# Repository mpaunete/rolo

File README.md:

# ROLO

A two-wheeled self-balancing robot built around an ESP32, with stepper motors, a servo arm,
a Bluetooth gamepad, live telemetry over WiFi, and the ability to stand itself up after a fall.

> **Early version, work in progress.** The electronics mostly work: you can pair a gamepad
> and drive ROLO around, and it balances and stands itself up. But this is a first version,
> some improvements are already needed, and much is still being built, tuned and redesigned.
> Expect things to change, and some parts of this repository to be incomplete.
> See [Current status](#current-status).

## Inspiration and goals

ROLO started from the [JJRobots B-Robot EVO 2](https://www.jjrobots.com/b-robot-evo-2-much-more-than-a-self-balancing-robot/)
and the [Kidbuild balance robot kit](https://www.kidbuild.de/balance-robot-kit/). I decided to
rebuild them and improve the electronics, with these goals:

- **Quieter motors:** TMC2209 stepper drivers.
- **Maximum customisation:** most of the parts redesigned in FreeCAD.
- **More sensors and accessories** than the original designs allow.
- **AI experimentation:** a face, voice, vision and a personality, in the spirit of Anki Vector.
- **A 3S battery,** and better battery management later (for example, charging without
  unplugging it).
- **Learning:** about balancing control and about AI on small robots.
- **A robotics platform for kids:** children can program ROLO themselves with
  [UIFlow](https://uiflow2.m5stack.com/) (M5Stack's block editor and MicroPython) on the
  M5Stack head, driving the robot through the same commands as the gamepad and the web pages.

## Videos

The full clip, from the stand-up to driving around:
[rolo-driving.mp4](docs/images/rolo-driving.mp4) (22 s, no sound).

## Current status

| area | status |
|---|---|
| balancing | working, tuned from recorded data |
| driving (gamepad and web joystick) | working; faster driving and steering feel still being tuned |
| standing up from lying face-down | working (arm push + wheel kick), still being refined |
| telemetry, recorder and analysis tools | working |
| web pages (drive, calibration with terminal, gamepad) | working |
| battery warnings | working |
| controller PCB (KiCad) | first version: mostly works, improvements needed (see below); files in `electronics/` |
| mechanical parts (FreeCAD) | designed, not yet published here |
| head: face, camera, microphones (M5Stack CoreS3) | hardware chosen, firmware not started |
| voice, vision, AI | planned |
| second robot and games | planned |
| battery management (charging in place) | planned |
| kids' programming (UIFlow on the M5Stack head) | planned |

### Known issues in the first electronics version

- The servo shares the 5 V supply with the logic. When it pulls hard, the supply dips enough
  to disturb WiFi and the IMU. A capacitor at the servo, or a separate supply for it, is needed.
- Few spare GPIOs are left on the controller for new sensors and accessories.
- No charging in place yet: the battery has to be unplugged to charge.

The planned fixes for the electronics and the mechanical parts are listed in
[docs/next-revision.md](docs/next-revision.md).

## Features

- **Balancing** with a cascaded controller: an angle loop (PD on a filtered gyro) inside a
  speed loop, with an acceleration feed-forward so the robot leans into speed changes.
- **Driving** from a gamepad or a web joystick, with a speed ramp shared by acceleration and
  braking.
- **Standing up** from lying face-down: the arm pushes the body up, a wheel kick drives under
  it, and the balance loop takes over mid-way, braking with a deeper lean afterwards.
- **Safety**: tilt cut-off, runaway detection, a command timeout, and battery warnings
  (LEDs and web pages).
- **Web pages** served by the robot: drive (joystick), calibration (live values, parameters,
  a terminal), and a gamepad debug page.
- **200 Hz telemetry stream** with a PC recorder and an analysis script, used to tune
  everything from measured data.
- **One command console** shared by the serial port and the web terminal.

## Repository layout

| folder | contents |
|---|---|
| `firmware/controller/` | the body's firmware: balancing, driving, arm, stand-up, web pages (PlatformIO, C++) |
| `firmware/common/link/` | shared by the body and the heads: the messages on the body–head UART link |
| `firmware/head-c3lcd/` | head: ESP32-C3 SuperMini with a Waveshare 2" LCD (the current head; code to be added) |
| `firmware/head-cores3/` | head: M5Stack CoreS3 (face, camera, microphones, speaker) |
| `firmware/head-seeed/` | head: ESP32-S3 DevKitC with a Seeed Grove Vision AI V2 and a ReSpeaker Lite |
| `firmware/tools/` | `rolo_stream.py` (recorder and test runner), `analyze.py` (report and plots) |
| `electronics/` | KiCad project for the controller board, Gerbers in `Output/` |
| `mechanical/` | mechanical design, FreeCAD (to be added) |
| `docs/` | documentation; [next-revision.md](docs/next-revision.md) lists the planned hardware changes; `images/` has the photos and videos |

## Hardware

| part | notes |
|---|---|
| ESP32 (DevKit V1, classic ESP32) | dual core: control loop on core 1, WiFi/web/LEDs on core 0 |
| 2 × TMC2209 stepper drivers | UART-configured, 1/16 microstepping, 900 mA RMS |
| 2 × NEMA17 steppers (42HD4027-01, 1.5 A) | 93.2 mm wheels |
| MPU6050 IMU | ±1000 °/s gyro, complementary filter |
| hobby servo | the arm (also used to stand up) |
| 3 × WS2812 LEDs | network, robot state, effort / battery warning |
| 3S LiPo | voltage divider (100k/22k) on GPIO 35 |
| Mini560 buck converter | 5 V for the logic and the servo |
| Bluetooth gamepad | a Switch Pro style controller, via Bluepad32 (classic Bluetooth) |

Main pin assignments are in [`firmware/controller/include/config.h`](firmware/controller/include/config.h).

## Building and flashing

Requires [PlatformIO](https://platformio.org/) (the VS Code extension or the CLI).

```bash
cd firmware/controller
pio run -t upload
```

The project uses the Bluepad32 Arduino core (classic Bluetooth gamepad support), which
PlatformIO downloads automatically through `platform_packages` in `platformio.ini`.

## First setup

1. Lay the robot down and power it on. It calibrates the IMU lying still (about 3 s), then
   the status LEDs show the network and robot state.
2. Connect WiFi from the serial console (115200 baud):

   ```
   wifi <ssid> <password>
   net
   ```

   Without a configured network it starts its own access point **`rolo`**
   (password **`rolorolo`**). That password is public, so change it on first use:

   ```
   apname <name>
   appass <password>
   ```

   The password must be at least 8 characters. Both are saved on the robot.
3. Open `http://<robot-ip>/` for the drive page. The calibration page (`/calibration`) has
   the parameters and a terminal; `/gamepad` helps with pairing.
4. Stand the robot up; it starts balancing once it is near upright.

## Console commands

The same commands work on the serial port and in the web terminal (`help` lists them):

| command | what it does |
|---|---|
| `set <name> <value>`, `list`, `save`, `load`, `reset` | tuning parameters (`save` only while lying down) |
| `arm up` / `arm down` | the arm |
| `kick [accel] [speed] [angle]` | stand up from lying face-down |
| `pad pair on\|off`, `pad forget`, `pad rumble` | gamepad pairing |
| `motors`, `motortest <steps/s> [seconds] [accel]` | driver status, spin the wheels with the robot held up |
| `net`, `wifi`, `forget`, `apname`, `appass` | network |
| `mem` | free memory |

## Tools

```bash
cd firmware/tools
python -m venv .venv
.venv/bin/pip install -r requirements.txt

# record 30 s of the 200 Hz stream
.venv/bin/python rolo_stream.py <robot-ip> --seconds 30 --name my-run

# run a repeatable test (still, step, tap, turn, ramp, all) and analyse it
.venv/bin/python rolo_stream.py <robot-ip> --test step --amount 0.5 --name step-1
.venv/bin/python analyze.py step-1
```

Each recording produces `<name>.csv` (samples), `<name>-events.csv` (commands and events) and
`<name>-params.json` (the parameters at the time). `analyze.py` prints a report (timing,
stillness, pushes, drive steps, limits) and saves a plot.

## Roadmap

- **Heads**: interchangeable heads on the same body, linked over UART: a plain ESP32-C3
  with a 2-inch LCD, an M5Stack CoreS3 (face, camera, microphones, speaker) and a Seeed Studio
  vision head. They share one firmware project with a build per head, and each head tells
  the body what it can do. Later: offline voice (wake word and commands), vision, and WiFi
  moved from the body to the head.
- **Optional AI**: a local server for conversation and speech, or an on-robot LLM module.
- **Games**: two robots, a referee page, and living-room battles (knock off the other robot's
  accessories, jousting, IR tag).
- **Kids' programming**: UIFlow on the CoreS3 head, with blocks for driving, the arm, the
  LEDs and the robot's events (fell over, stood up, battery low), so children can write their
  own behaviours and games.

## Licence

[MIT](LICENSE), for now, covering the whole repository. Separate licences for the hardware
files (electronics and mechanical) may follow.

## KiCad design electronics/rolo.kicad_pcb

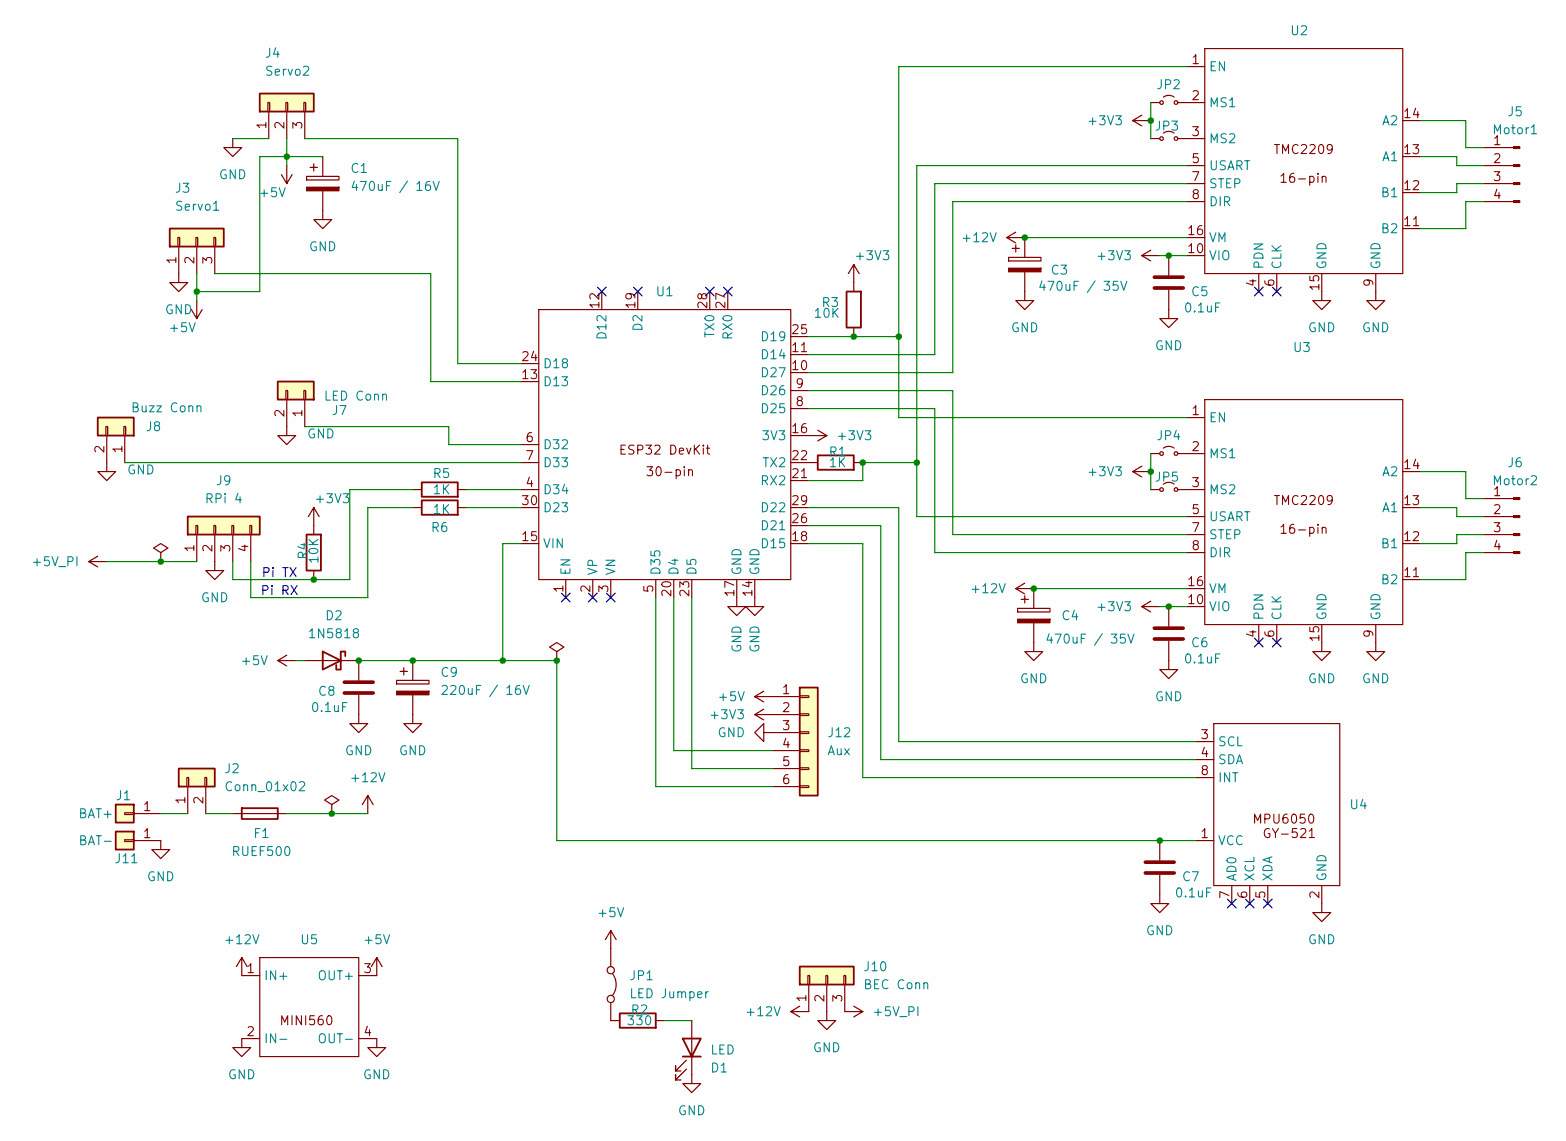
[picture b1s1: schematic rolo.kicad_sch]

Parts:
C1: 470uF / 16V; CP_Radial_D8.0mm_P3.50mm
C3, C4: 470uF / 35V; CP_Radial_D8.0mm_P3.50mm
C5, C6, C7, C8: 0.1uF; C_Disc_D5.0mm_W2.5mm_P5.00mm
C9: 220uF / 16V; CP_Radial_D8.0mm_P3.50mm
D1: LED; LED_D3.0mm
D2: 1N5818; D_DO-41_SOD81_P10.16mm_Horizontal
F1: RUEF500; Fuse_RUEF500
J1: BAT+; MountingHole_2.2mm_M2_Pad
J2: Conn_01x02; AMASS_XT30U-M_1x02_P5.0mm_Vertical
J3: Servo1; PinHeader_1x03_P2.54mm_Vertical
J4: Servo2; PinHeader_1x03_P2.54mm_Vertical
J5: Motor1; PinHeader_1x04_P2.54mm_Vertical
J6: Motor2; PinHeader_1x04_P2.54mm_Vertical
J7: LED Conn; JST_XH_B2B-XH-A_1x02_P2.50mm_Vertical
J8: Buzz Conn; JST_XH_B2B-XH-A_1x02_P2.50mm_Vertical
J9: RPi 4; JST_XH_B4B-XH-A_1x04_P2.50mm_Vertical
J10: BEC Conn; JST_XH_B3B-XH-A_1x03_P2.50mm_Vertical
J11: BAT-; MountingHole_2.2mm_M2_Pad
J12: Aux; PinHeader_1x06_P2.54mm_Vertical
JP1: LED Jumper; PinHeader_1x02_P2.54mm_Vertical
JP2, JP4: MS1 EN; PinHeader_1x02_P2.54mm_Vertical
JP3, JP5: MS2 EN; PinHeader_1x02_P2.54mm_Vertical
R1, R5, R6: 1K; R_Axial_DIN0207_L6.3mm_D2.5mm_P10.16mm_Horizontal
R2: 330; R_Axial_DIN0207_L6.3mm_D2.5mm_P10.16mm_Horizontal
R3, R4: 10K; R_Axial_DIN0207_L6.3mm_D2.5mm_P10.16mm_Horizontal
U1: ESP32_DevKit_30Pin
U2, U3: TMC2209_16Pin
U4: MPU6050_Conn
U5: MINI560_5V_8Pin

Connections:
+3V3: C5.1, C6.1, J12.2, JP2.1 (A), JP3.1 (A), JP4.1 (A), JP5.1 (A), R3.2, R4.2, U1.16 (3V3), U2.10 (VIO), U3.10 (VIO)
+5V: C1.1, D2.2 (A), J3.2, J4.2, J12.1, JP1.1 (A), U5.3 (OUT+)
+5V_PI: J9.1, J10.3
+12V: C3.1, C4.1, F1.1, J10.1, U2.16 (VM), U3.16 (VM), U5.1 (IN+)
GND: C1.2, C3.2, C4.2, C5.2, C6.2, C7.2, C8.2, C9.2, D1.1 (K), J3.1, J4.1, J7.2, J8.2, J9.2, J10.2, J11.1 (Pin_1_1), J12.3, U1.14 (GND), U1.17 (GND), U2.9 (GND), U2.15 (GND), U3.9 (GND), U3.15 (GND), U4.2 (GND), U5.2 (IN-), U5.4 (OUT-)
unnamed: D1.2 (A), R2.2
unnamed: C7.1, C8.1, C9.1, D2.1 (K), U1.15 (VIN), U4.1 (VCC)
unnamed: J1.1 (Pin_1_1), J2.1
unnamed: F1.2, J2.2
unnamed: J3.3, U1.13 (D13)
unnamed: J4.3, U1.24 (D18)
unnamed: J5.1, U2.14 (A2)
unnamed: J5.2, U2.13 (A1)
unnamed: J5.3, U2.12 (B1)
unnamed: J5.4, U2.11 (B2)
unnamed: J6.1, U3.14 (A2)
unnamed: J6.2, U3.13 (A1)
unnamed: J6.3, U3.12 (B1)
unnamed: J6.4, U3.11 (B2)
unnamed: J7.1, U1.6 (D32)
unnamed: J8.1, U1.7 (D33)
unnamed: J9.3, R4.1, R5.1
unnamed: J9.4, R6.1
unnamed: J12.4, U1.20 (D4)
unnamed: J12.5, U1.23 (D5)
unnamed: J12.6, U1.5 (D35)
unnamed: JP1.2 (B), R2.1
unnamed: JP2.2 (B), U2.2 (MS1)
unnamed: JP3.2 (B), U2.3 (MS2)
unnamed: JP4.2 (B), U3.2 (MS1)
unnamed: JP5.2 (B), U3.3 (MS2)
unnamed: U1.11 (D14), U2.7 (STEP)
unnamed: U1.18 (D15), U4.8 (INT)
unnamed: R3.1, U1.25 (D19), U2.1 (EN), U3.1 (EN)
unnamed: U1.26 (D21), U4.4 (SDA)
unnamed: U1.29 (D22), U4.3 (SCL)
unnamed: R6.2, U1.30 (D23)
unnamed: U1.8 (D25), U3.8 (DIR)
unnamed: U1.9 (D26), U3.7 (STEP)
unnamed: U1.10 (D27), U2.8 (DIR)
unnamed: R5.2, U1.4 (D34)
unnamed: R1.2, U1.21 (RX2), U2.5 (USART), U3.5 (USART)
unnamed: R1.1, U1.22 (TX2)

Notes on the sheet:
Pi TX
Pi RX

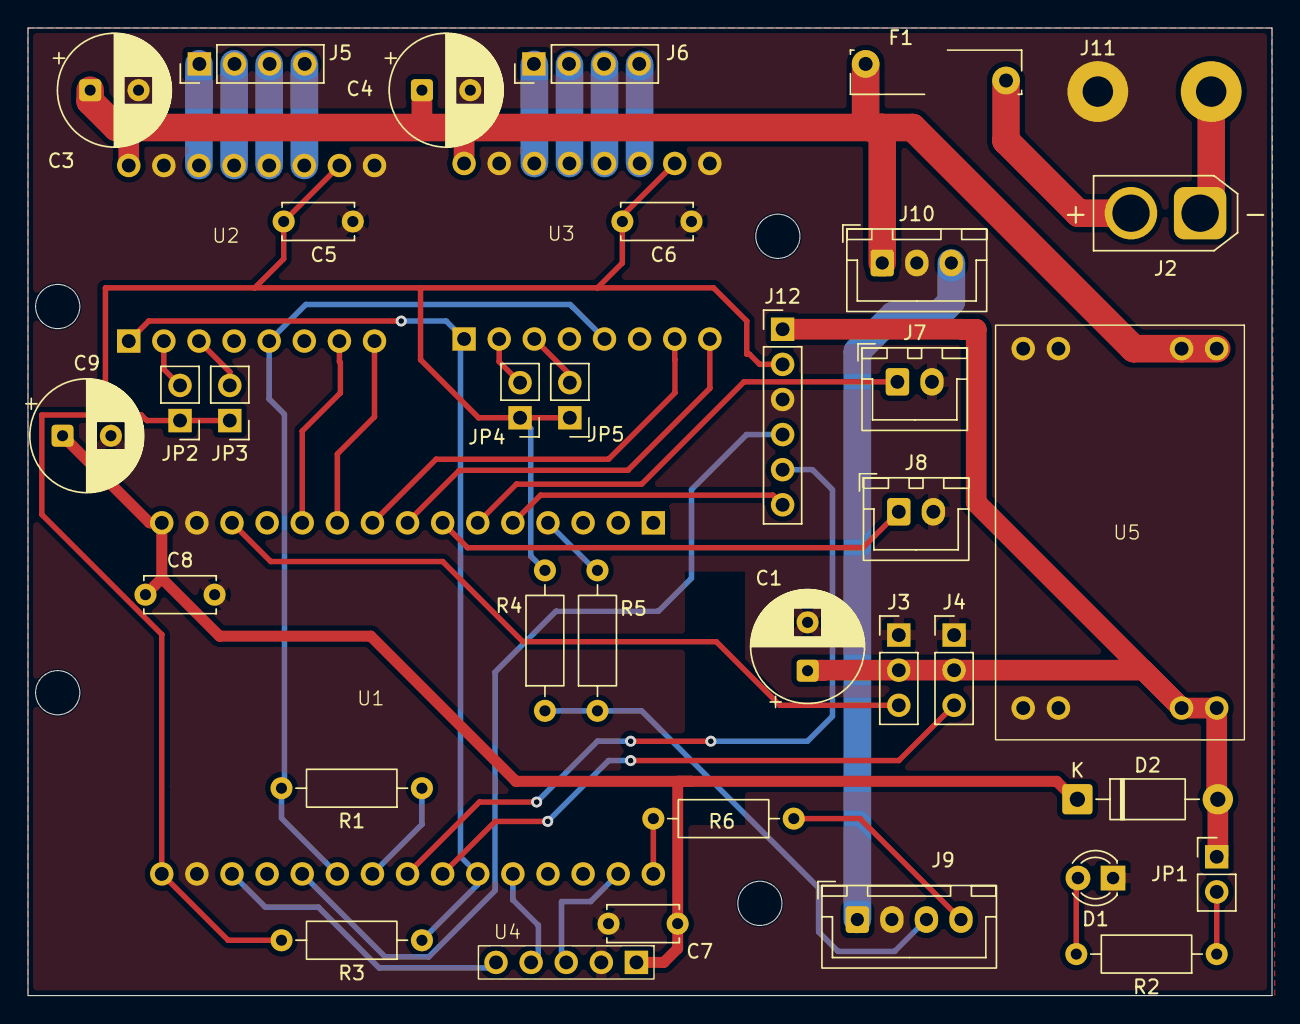
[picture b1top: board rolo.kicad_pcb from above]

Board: 2 copper layers, 90.0 x 70.0 mm, 39 parts (1 on the bottom side), 43 nets.
